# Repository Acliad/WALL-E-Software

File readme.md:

# Overview
This repo contains code, PCB files, and some 3D files for a WALL-E robot. The robot is controlled by an ESP32 microcontroller with PlayStation Navigation controllers. 3D files can be found under the `Mechanical` folder. The PCB files can be found under the `PCB Files`. The code can be found under the `src` folder. 

This readme file contains information on setting up and using WALL-E, and there are several videos in the `Docs` folder that give examples.

The code is written as an Arduino sketch, but has many C++ files and classes. The custom library code is located in the `src` folder of the walle sketch and is organized into the following folders:
- `audio`: Contains the code for the audio player.
- `display`: Contains the code for the display and animations.
- `motion`: Contains the code for the motion animations.
- `button`: Contains the code for the button handling.
- `controller`: Contains the code for the controller handling.
- `stats`: Contains a simple stats class mostly used for debugging.

Additionally, the root of the `src` folder contains the main sketch file, `walle.ino`, which is the entry point for the program. It also contains several files to help configure WALL-E:
- `config.hpp`: Contains the configuration for the audio player, display, and controller.
- `display_animations.hpp` and `display_animations.cpp`: Contains code for programatically defining display animations.
- `motion_animations.hpp` and `motion_animations.cpp`: Contains code for programatically defining motion animations.

# Button Mapping
This image can be found in `Docs/Images`.

# Setting up Arduino IDE
This project uses a special board package for the ESP32 called [Bluepad32](https://github.com/ricardoquesada/bluepad32). To install it, you need to add this board to your Arduino IDE. The abreviated steps to do this are below. See [this doc page](https://bluepad32.readthedocs.io/en/latest/plat_arduino/) for more detailed instructions.
1. Open the Arduino IDE settings and add the following two URLs to the "Additional Boards Manager URLs" field: 
`https://raw.githubusercontent.com/espressif/arduino-esp32/gh-pages/package_esp32_index.json`
`https://raw.githubusercontent.com/ricardoquesada/esp32-arduino-lib-builder/master/bluepad32_files/package_esp32_bluepad32_index.json`
2. Install the ESP32 and ESP32 Bluepad32 boards from the Boards Manager.
3. Select the `ESP32-WROOM-DA Module` from the Tools > Board > esp32_bluepad32 menu.

You will also need to install the following libraries:
- Adafruit PWM Servo Driver Library
- DFPlayer Mini Mp3 by Makuna
- Ramp
- ServoESP32
- TFT_eSPI

You will need to setup the TFT_eSPI library with the correct config. To do this, create a `TFT_eSPI_Setups` folder in your Arduino libraries folder (usualy in `~/Documents/Arduino/libraries/`), then copy the `TFT_eSPI_walle_setup.h` file in `src/display/` to this new folder. After that, open User_Setup_Select.h in the `/TFT_eSPI/` library folder and comment out the current user config (`User_Setup.h` by default), then add the following line:
```cpp
 #include <../TFT_eSPI_Setups/TFT_eSPI_walle_setup.h>
 ```

After this, you should be able to compile and upload the code to the ESP32. Make sure WALL-E is powered on before plugging in the USB cable to the ESP32, otherwise the USB port will attempt to power the servo motors and will likely trip your USB port's overcurrent protection.

Note that the Arduino IDE will throw some warnings related to "converting a string constant to 'char*'" as well as some bluepad and eSPI_TFT warnings. These can be ignored.

# Adding new sounds
New sounds can be added to the audio player's SD card as `.mp3` files. Audio tracks must be labeled as numbers with the format `0001.mp3`, `0002.mp3`, etc. The number of the audio track is the index that will be used to play the sound. You can configure the audio player sounds and keybindings in the `config.hpp` file. Here is what the folder structure on the SD card should look like:

For instance, if you add a track `0011.mp3` and you wish to bind it to the `L2 + Up` button, you would add the following line to the `config.hpp` file:
```cpp
const int audio_track_selection_list[] = {
    TRACK_INDEX_EVE_1, // Up
    TRACK_INDEX_TADA, // Right
    TRACK_INDEX_SCREAM, // Down
    TRACK_INDEX_WALLE_1, // Left
    11, // L2 + Up <<<<<<<<<<<<<<<<<<<<<<<< CHANGED TRACK 
    TRACK_INDEX_EVE_3, // L2 + Right
    TRACK_DEFINE_DANCING, // L2 + Down
    TRACK_LA_VIE_EN_ROSE, // L2 + Left
};
```

Sounds which are bound to a button can be added to keyframes in motion animations. 

Similarly, you could add it to the audio_track_random_list. 

```cpp
// Tracks in this array will be selected randomly by the playRandomTrack() function
const int audio_track_random_list[] = {
    TRACK_INDEX_EVE_1,
    TRACK_INDEX_EVE_2,
    TRACK_INDEX_EVE_3,
    TRACK_INDEX_WALLE_1,
    TRACK_INDEX_SCREAM,
    TRACK_INDEX_TADA,
    11 // <<<<<<<<<<<<<<<<<<<<<<<< ADDED TRACK
};
```

# Adding solar animations
The steps to add a solar animation are as follows:
1. Declare your variable name in display_animations.hpp:
```cpp
extern AnimateLeve animate_display_startup;
...
// Add your variable name here
extern AnimateLevel my_animation;
```
2. Define your vairable in display_animations.cpp:
```cpp
AnimateLevel animate_display_startup = AnimateLevel();
...
// Define your variable here
AnimateLevel my_animation = AnimateLevel();
```
3. Create a setup_my_animation() function in display_animations.cpp:
```cpp
void setup_my_animation() {
  my_animation.addKeyframe(0, 0);
  my_animation.addKeyframe(1000, 1);
  ...
}
```
4. Add your setup_my_animation() function to the setup_animations() function in display_animations.cpp:
```cpp
void setup_animations() {
  setup_startup();
  ...
  // Add your setup_my_animation() function here
  setup_my_animation();
}
```

Now your variable ```my_animation``` will be available to use in the main sketch. 

### Notes
- A keyframe with a single change will perform that change at the beginning of the keyframe. For example, if 2 bars are on and you request 3 to be on with a duration of 1 second, the 3rd bar will turn on immediately and the keyframe will wait for 1 second to complete. If you have two or more changes in a keyframe, the changes will be evenly distributed throughout the duration of the keyframe, ending with a change. For example, if 2 bars are on and you request 5 to be on with a duration of 1 second, the 3rd bar will turn on immediately, the 4th bar will turn on after 0.5 seconds, and the 5th bar will turn on after 1 second.
- The sun's status is always evaluated at the beginning of a keyframe.

# Adding motion animations
The steps to add a motion animation are as follows:
1. Declare your variable name in motion_animations.hpp:
```cpp
namespace MotionAnimations {
    // Add custom animations here:
    extern ServoAnimation my_animation;

    // Rest of namespace ...
}
```
2. Define your vairable in motion_animations.cpp:
```cpp
namespace MotionAnimations {
    // Define new animations here

    ServoAnimation my_animation = ServoAnimation();

    // Rest of namespace ...
}
```
3. Create a setup_my_animation() function in motion_animations.cpp. Keyframes are created one at a time and then added to the previously created animation. Create a keyframe with `ServoKeyframe *my_keyframe = new ServoKeyframe(duration_ms);`. Add the servo positions to the keyframe with `my_keyframe->add_servo_scaler(servo_ptr, position);`. Add the keyframe to the animation with `my_animation.addKeyframe(my_keyframe);`. Servos are addressed by their name. There is a #define for each servo. E.g, to get the left eye servo you would use `servos.map[SERVO_EYE_LEFT_NAME]` For example:
```cpp
// Create setup functions for each animation.
// NOTE: Don't forget to call these functions in setup_animations().
void setup_my_animation() {
    // Rotate eyes in opposite directions
    ServoKeyframe *my_keyframe1 = new ServoKeyframe(1000);
    my_keyframe->add_servo_scaler(servos.map[SERVO_EYE_LEFT_NAME], 0.75);
    my_keyframe->add_servo_scaler(servos.map[SERVO_EYE_RIGHT_NAME], -0.75);
    
    // Pause for 3 seconds
    ServoKeyframe *my_keyframe2 = new ServoKeyframe(3000);

    // Return the eyes to their original position
    ServoKeyframe *my_keyframe3 = new ServoKeyframe(1000);
    my_keyframe->add_servo_scaler(servos.map[SERVO_EYE_LEFT_NAME], 0);
    my_keyframe->add_servo_scaler(servos.map[SERVO_EYE_RIGHT_NAME], 0);

    // Add the keyframes to the animation
    my_animation.add_keyframe(my_keyframe1);
    my_animation.add_keyframe(my_keyframe2);
    my_animation.add_keyframe(my_keyframe3);
}
```
4. Add your setup_my_animation() function to the setup_animations() function in motion_animations.cpp:
```cpp
void setup_animations(ServoContext servos) {
    // This function should get called in the main setup() function. It calls all animation setup functions for use in
    // the main sketch.

    // Add setup functions for new animations here
    setup_my_animation();

    // Rest of animation setups...
}
```
5. Play the animation with `servo_player.play(&MotionAnimations::my_animation);`. Alternatively, you can add the animation to the `head_animations` array in the main sketch to bind it to a button press:
```cpp
ServoAnimation         *head_animations[] = {
    &MotionAnimations::my_animation, // Up
    nullptr,      // Right
    nullptr,      // Down
    nullptr,      // Left
    nullptr,      // L2 + Up
    nullptr,      // L2 + Right
    nullptr,      // L2 + Down
    nullptr       // L2 + Left
};
```

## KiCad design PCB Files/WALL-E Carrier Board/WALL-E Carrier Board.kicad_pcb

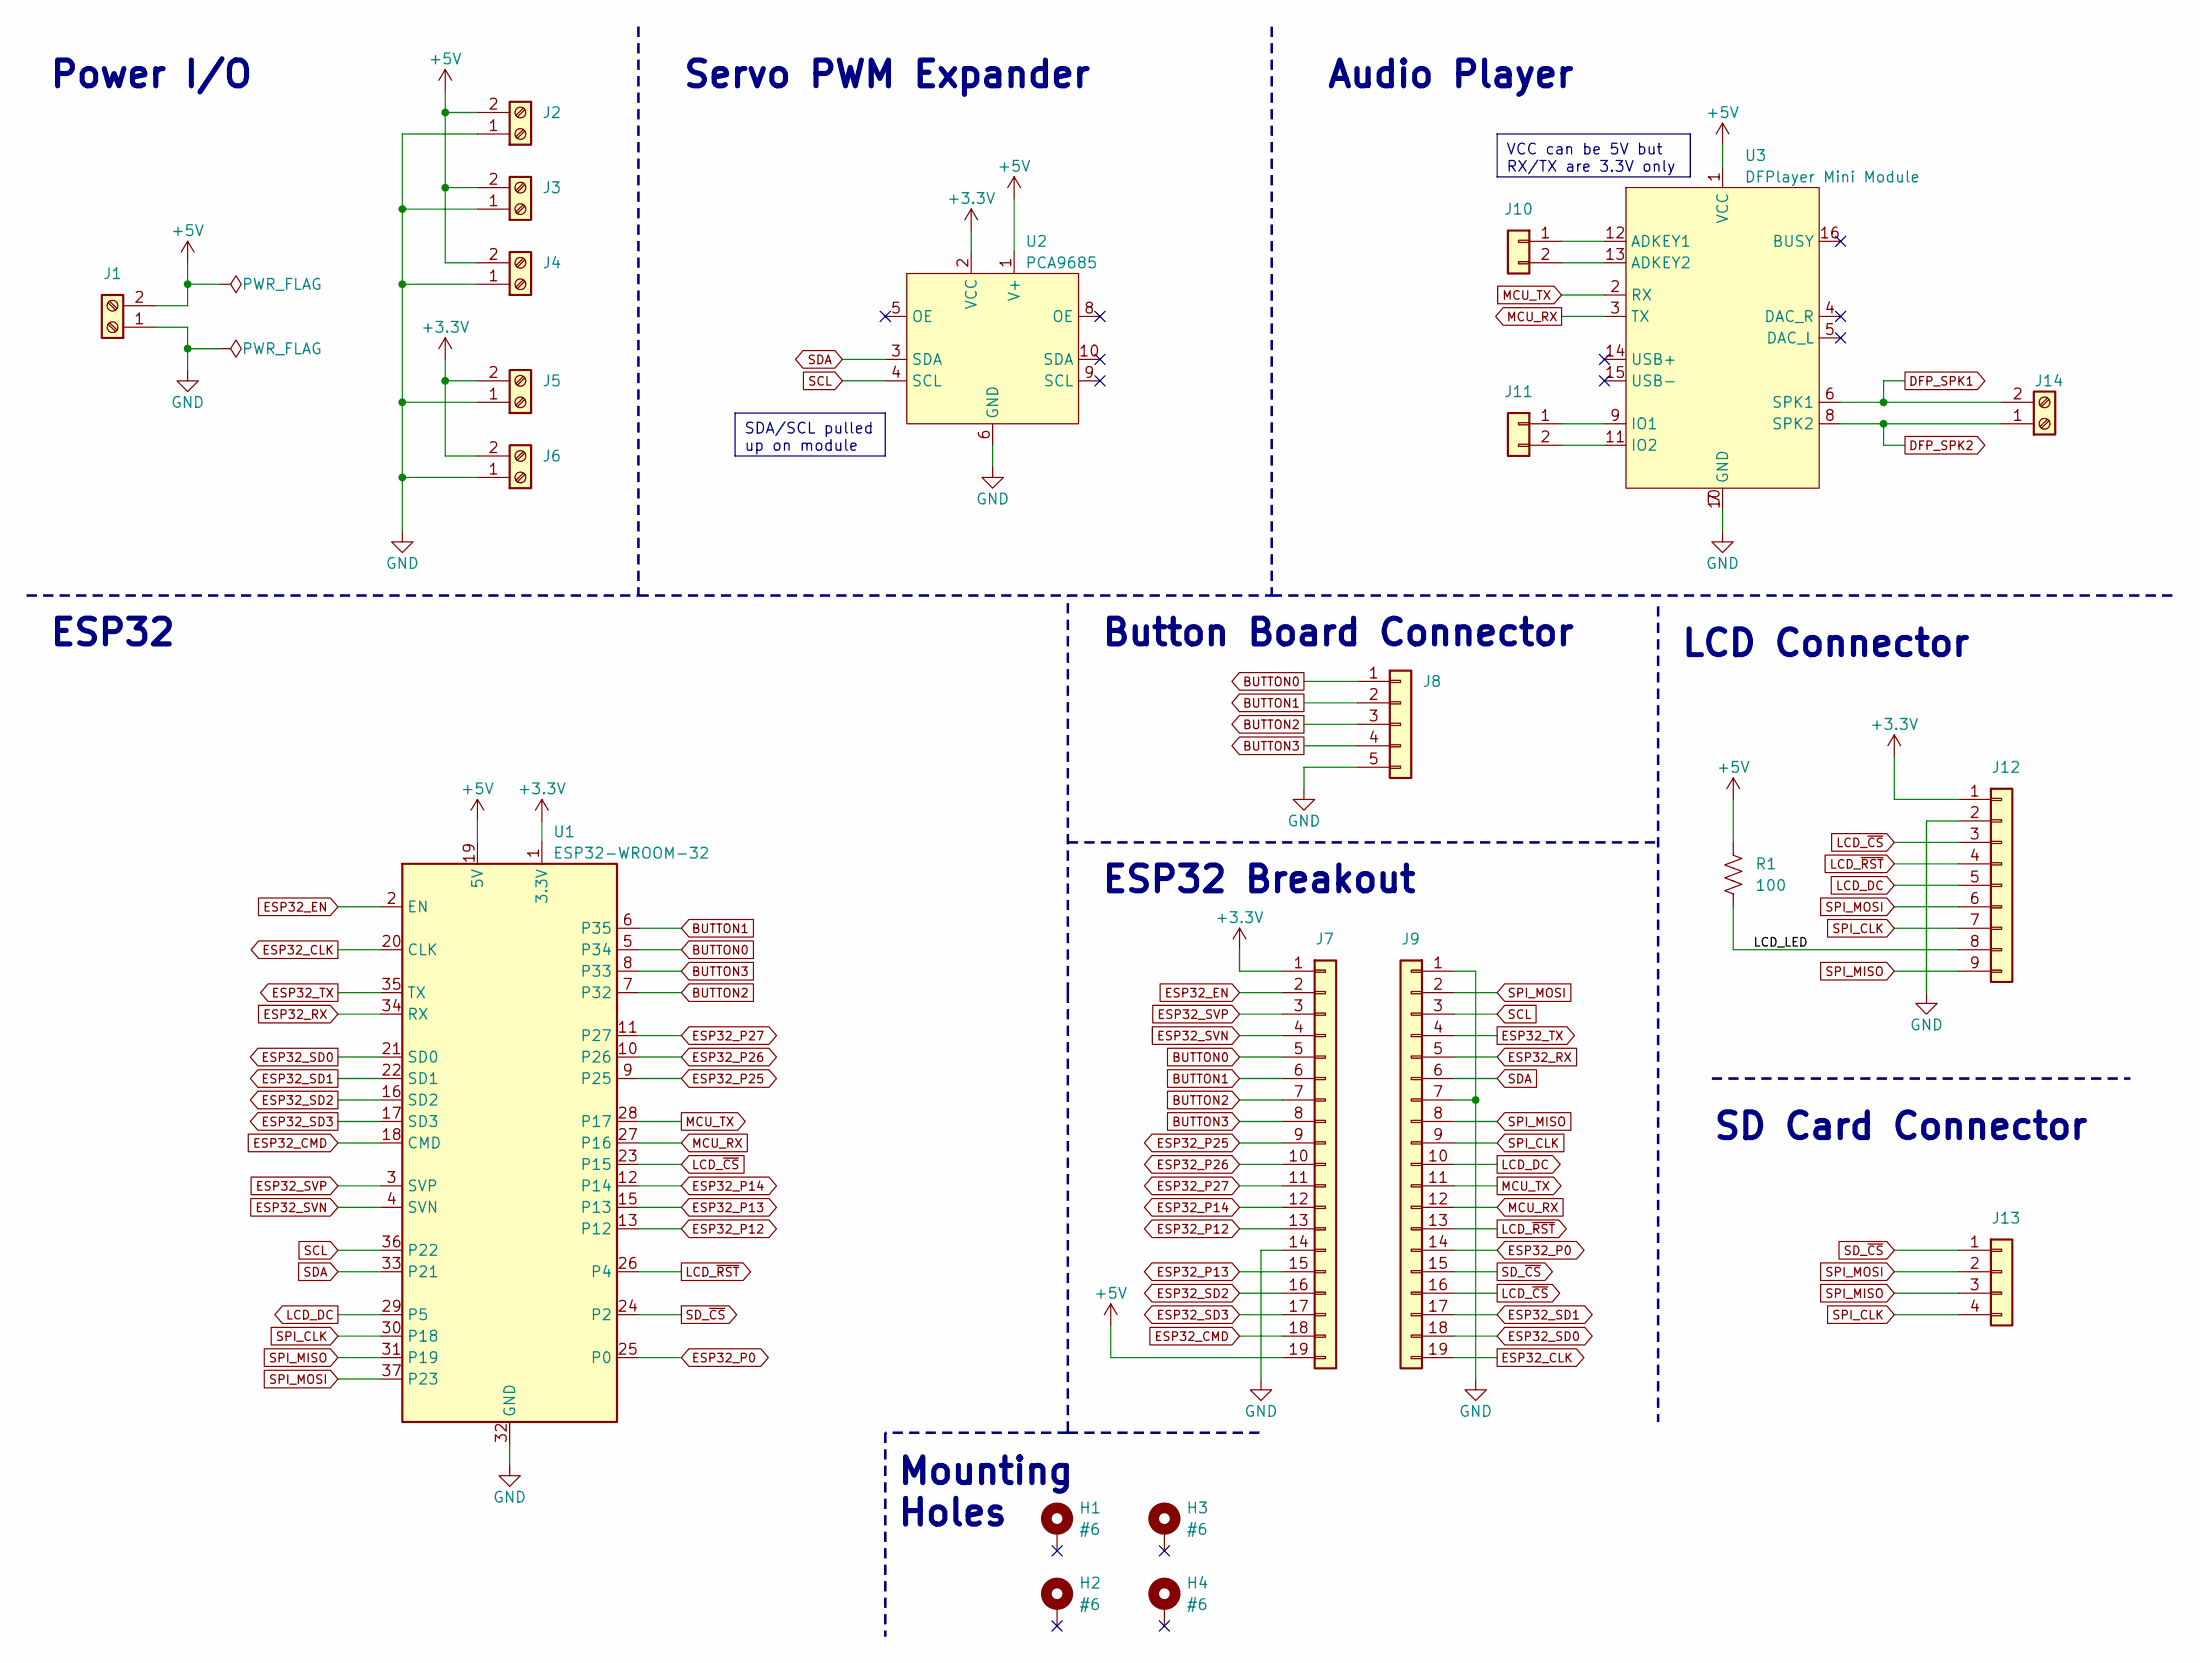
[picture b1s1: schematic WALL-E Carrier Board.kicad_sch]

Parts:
H1, H2, H3, H4: #6; MountingHole_3.7mm_Pad
J1, J2, J3, J4, J5, J6, J14: Screw_Terminal_01x02; TerminalBlock_MetzConnect_Type011_RT05502HBWC_1x02_P5.00mm_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
J7, J9: Conn_01x19; PinHeader_1x19_P2.54mm_Vertical
J8: Conn_01x05; PinHeader_1x05_P2.54mm_Vertical
J10, J11: Conn_01x02; PinHeader_1x02_P2.54mm_Vertical
J12: Conn_01x09; PinHeader_1x09_P2.54mm_Vertical
J13: Conn_01x04; PinHeader_1x04_P2.54mm_Vertical
R1: 100; R_Axial_DIN0207_L6.3mm_D2.5mm_P10.16mm_Horizontal
U1: ESP32-WROOM-32; HiLetgo ESP-32S Module
U2: PCA9685; Adafruit PCA9685 rev C
U3: DFPlayer Mini Module

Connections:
+3.3V: J5.2, J6.2, J7.1, J12.1, U1.1 (3.3V), U2.2 (VCC), U2.11 (VCC)
+5V: J1.2, J2.2, J3.2, J4.2, J7.19, R1.1, U1.19 (5V), U2.1 (V+), U2.12 (V+), U3.1 (VCC)
/LCD_LED: J12.8, R1.2
BUTTON0: J7.5, J8.1, U1.5 (P34)
BUTTON1: J7.6, J8.2, U1.6 (P35)
BUTTON2: J7.7, J8.3, U1.7 (P32)
BUTTON3: J7.8, J8.4, U1.8 (P33)
DFP_SPK1: J14.2, U3.6 (SPK1)
DFP_SPK2: J14.1, U3.8 (SPK2)
ESP32_CLK: J9.19, U1.20 (CLK)
ESP32_CMD: J7.18, U1.18 (CMD)
ESP32_EN: J7.2, U1.2 (EN)
ESP32_P0: J9.14, U1.25 (P0)
ESP32_P12: J7.13, U1.13 (P12)
ESP32_P13: J7.15, U1.15 (P13)
ESP32_P14: J7.12, U1.12 (P14)
ESP32_P25: J7.9, U1.9 (P25)
ESP32_P26: J7.10, U1.10 (P26)
ESP32_P27: J7.11, U1.11 (P27)
ESP32_RX: J9.5, U1.34 (RX)
ESP32_SD0: J9.18, U1.21 (SD0)
ESP32_SD1: J9.17, U1.22 (SD1)
ESP32_SD2: J7.16, U1.16 (SD2)
ESP32_SD3: J7.17, U1.17 (SD3)
ESP32_SVN: J7.4, U1.4 (SVN)
ESP32_SVP: J7.3, U1.3 (SVP)
ESP32_TX: J9.4, U1.35 (TX)
GND: J1.1, J2.1, J3.1, J4.1, J5.1, J6.1, J7.14, J8.5, J9.1, J9.7, J12.2, U1.14 (GND), U1.32 (GND), U1.38 (GND), U2.6 (GND), U2.7 (GND), U3.7 (GND), U3.10 (GND)
LCD_DC: J9.10, J12.5, U1.29 (P5)
LCD_~CS: J9.16, J12.3, U1.23 (P15)
LCD_~RST: J9.13, J12.4, U1.26 (P4)
MCU_RX: J9.12, U1.27 (P16), U3.3 (TX)
MCU_TX: J9.11, U1.28 (P17), U3.2 (RX)
unnamed: J10.1, U3.12 (ADKEY1)
unnamed: J10.2, U3.13 (ADKEY2)
unnamed: J11.1, U3.9 (IO1)
unnamed: J11.2, U3.11 (IO2)
SCL: J9.3, U1.36 (P22), U2.4 (SCL)
SDA: J9.6, U1.33 (P21), U2.3 (SDA)
SD_~CS: J9.15, J13.1, U1.24 (P2)
SPI_CLK: J9.9, J12.7, J13.4, U1.30 (P18)
SPI_MISO: J9.8, J12.9, J13.3, U1.31 (P19)
SPI_MOSI: J9.2, J12.6, J13.2, U1.37 (P23)

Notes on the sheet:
VCC can be 5V but RX/TX are 3.3V only
SDA/SCL pulled up on module
SD Card Connector
Mounting Holes
Power I/O
LCD Connector
Audio Player
Servo PWM Expander
ESP32 Breakout
Button Board Connector
ESP32

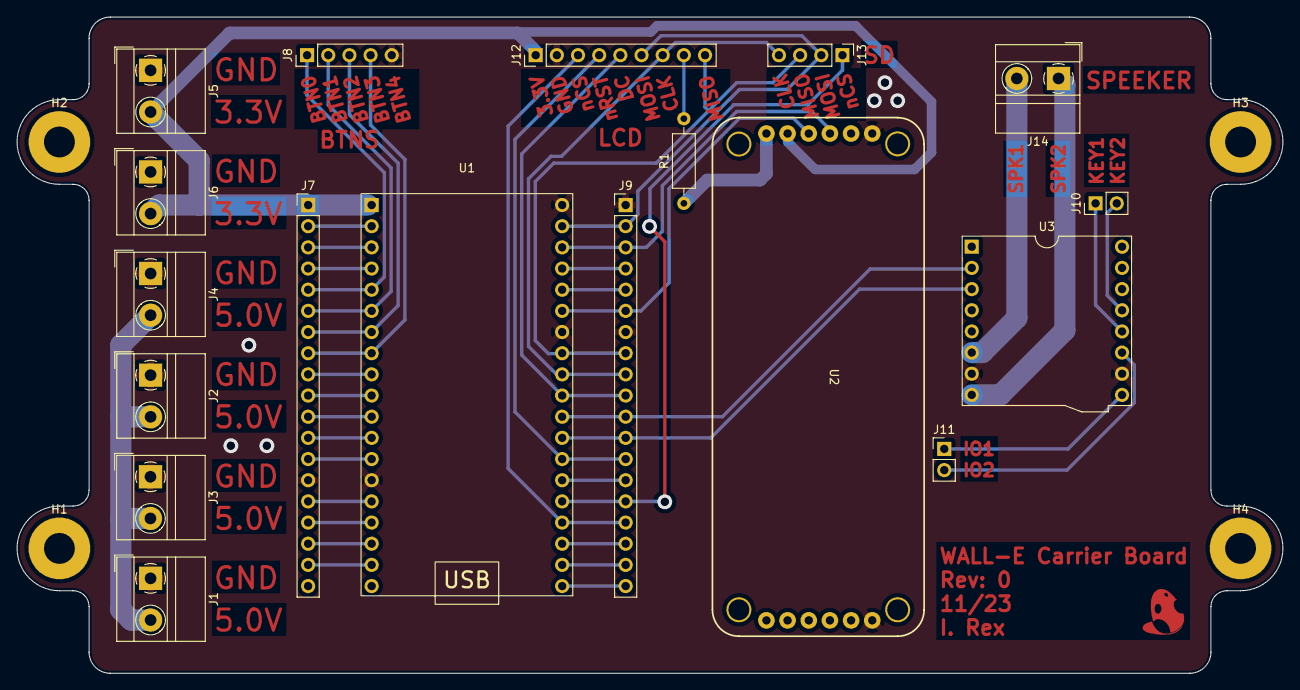
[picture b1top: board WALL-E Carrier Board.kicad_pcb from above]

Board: 2 copper layers, 151.9 x 78.7 mm, 22 parts (0 on the bottom side), 43 nets.

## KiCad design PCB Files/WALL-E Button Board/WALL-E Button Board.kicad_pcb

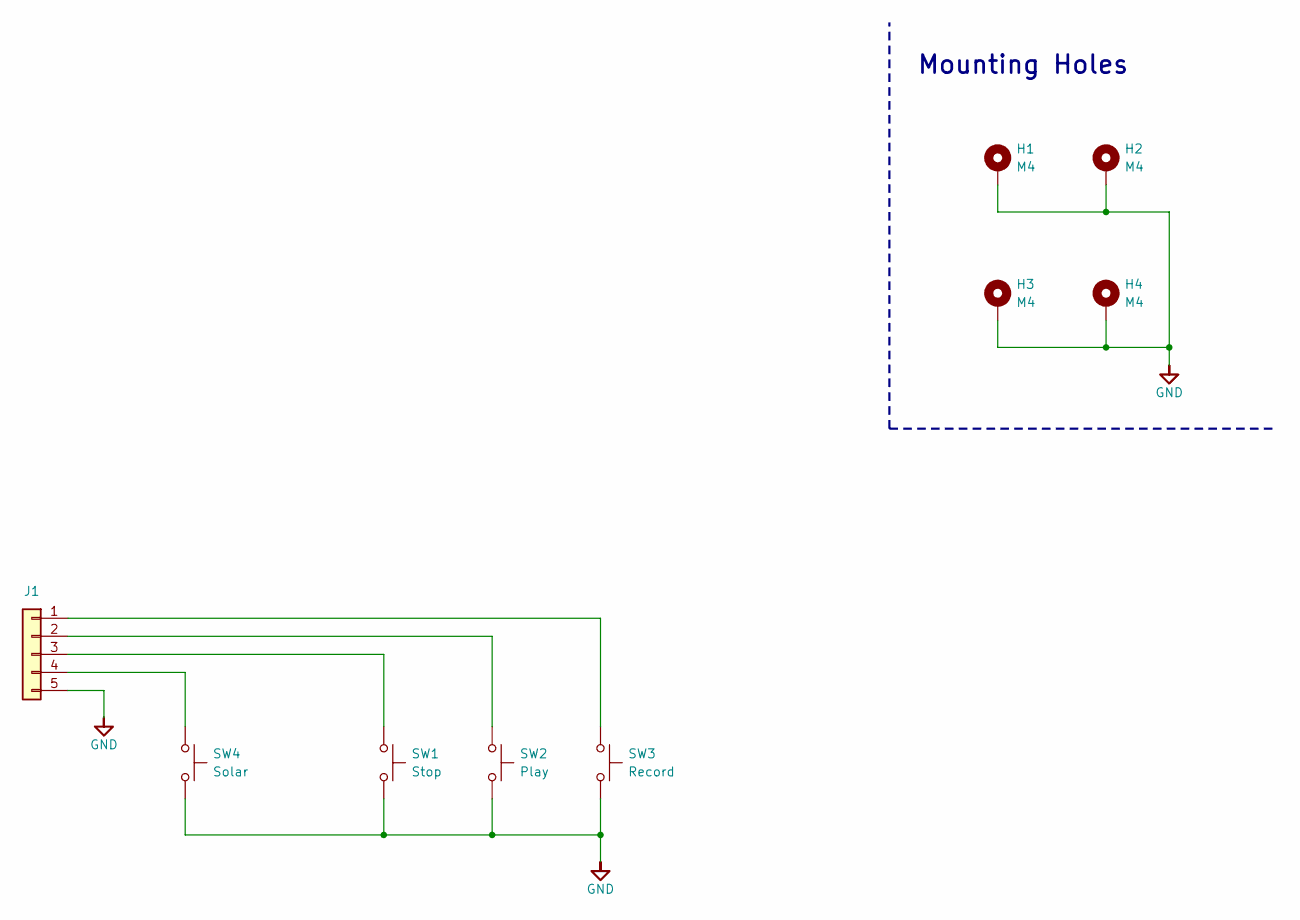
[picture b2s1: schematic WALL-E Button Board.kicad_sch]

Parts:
H1, H2, H3, H4: M4; MountingHole_4.3mm_M4_DIN965_Pad
J1: Conn_01x05; PinHeader_1x05_P2.54mm_Vertical
SW1: Stop; SW_Hotswap_Kailh_MX
SW2: Play; SW_Hotswap_Kailh_MX
SW3: Record; SW_Hotswap_Kailh_MX
SW4: Solar; SW_Hotswap_Kailh_MX

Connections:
GND: H1.1, H2.1, H3.1, H4.1, J1.5, SW1.2, SW2.2, SW3.2, SW4.2
unnamed: J1.1, SW3.1
unnamed: J1.2, SW2.1
unnamed: J1.3, SW1.1
unnamed: J1.4, SW4.1

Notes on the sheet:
Mounting Holes

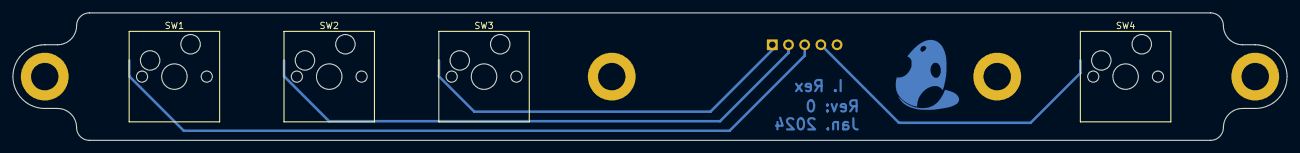
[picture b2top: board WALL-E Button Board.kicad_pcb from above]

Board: 2 copper layers, 200.0 x 20.0 mm, 9 parts (1 on the bottom side), 5 nets.

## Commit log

2023-09-04 Initialized main branch
2023-09-04 Initial commit of walle code
2023-10-01 Updated .gitignore
2023-10-08 Checkpoint before deleting motor.hpp/.cpp files
    Decided to go for a single class approach for the motor and another for the servos. At least for now. Cleaning up, but wanted to maintain the files in case I decide to go back.
2024-01-21 Moved code to /src/ folder
2024-01-21 Brought in display, updated controller, motor/servo code. Cleaned up
2024-01-21 Added PCBs and inital mechanical files
2024-01-27 Updated gitignore
2024-01-27 Integrated and cleaned. Updated solar display to match audio
2024-01-27 Added Docs and Sounds folders
2024-01-27 Cleaned PCB folder
2024-01-28 Added PDF of carrier board schematic
2024-01-28 Updated display to better reflect film
2024-01-28 Added font generator tool for eSPI library. Update .vscode setup
2024-01-28 Removed output directory from arduino.json
2024-01-28 Added class for buttons
2024-01-28 Added note to schematic about button pullups
2024-01-29 Added basic stats class
2024-02-01 Added normalized output option to controllers
2024-02-04 Mapped controlls and added more configs
2024-02-04 Added thumbsticks buttons to NavigationController class
2024-02-04 Added deadzone to NavigationController
2024-02-04 Controller mapable animations implemented
2024-02-04 Refactored solar_animations to display_animations
2024-02-04 Moved updating of motor speed from mapInputs() to updateAll()
2024-02-04 Updated missed references from refactor of display_animations
2024-02-04 Refactored animate_head to animate_servo
2024-02-06 Refactored display library in preperation for data display
2024-02-11 Updated thickness of button inserts to 0.4mm
2024-02-11 Added servo recorder. Still has some memory leaks
2024-02-11 Fix attempt for Bluetooth connection bug in gamepad controller
2024-02-15 Keyframe file saving as expected
2024-02-15 Files saving and loading as expected
2024-02-16 Added track saving and loading, moved MP3Notify to own class
2024-02-16 Added picture of buttons for reference
2024-02-18 Edit ServoAnimation mode added, changed ServoContext to a map
2024-02-18 Cleaned up display module
2024-02-20 Added doxygen documentation to all files
2024-02-27 Config adjustments after testing
2024-02-28 Updated standoff 3D model
2024-03-03 Updated documentation
2024-03-03 Moved readme.md to root, updated button map image
